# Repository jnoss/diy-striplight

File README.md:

# diy-striplight
PCB design files for a carrier board for a led to use as a diy striplight

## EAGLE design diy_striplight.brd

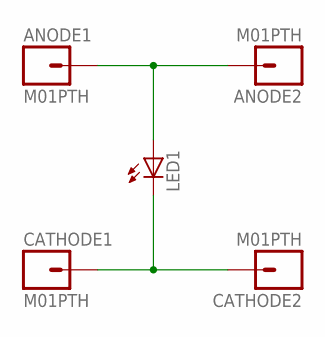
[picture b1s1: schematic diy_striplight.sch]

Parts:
ANODE1, ANODE2: M01PTH; 1X01
CATHODE1, CATHODE2: M01PTH; 1X01
LED1: LEDCHIPLED_0603; CHIPLED_0603

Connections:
unnamed: ANODE1.1, ANODE2.1, LED1.A
unnamed: CATHODE1.1, CATHODE2.1, LED1.C

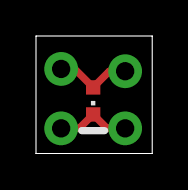
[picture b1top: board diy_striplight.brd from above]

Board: 2 copper layers, 6.5 x 6.5 mm, 5 parts (0 on the bottom side), 2 nets.

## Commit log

2016-08-29 setup eagle-preview-autogen
2016-08-29 add gitignore
2016-08-30 add to gitignore
2016-08-30 initial commit diy striplight

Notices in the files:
parts and their libraries:
SparkFun-Connectors: Licensing: CC v3.0 Share-Alike You are welcome to use this library for commercial purposes.
